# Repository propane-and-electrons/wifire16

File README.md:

wifire16
--------

After I wired up 16 MOSFET + optoisolator circuits on perfboard for Flux and Fire, I swore I was never going to do it by hand again. When it came time to make a similar circuit for Super Street Fire, I decided the only option was to make a PCB to wirelessly control 16 flame effects. The end result: the wifire16 board.

### Feature Summary

* Arduino compatible
* Programmable via 6-pin FTDI header or 6-pin ICSP header
* 16 PWM-capable DC load channels switched via MOSFET
* Wireless support with XBee or compatible radio, e.g. RN-XV WiFly
* All ATMega I/O pins are broken out on the board
* DC load power is optoisolated from the control system power
* Power connectors use 5mm screw terminals or Anderson Powerpole connectors
* Load power status is reported to the microcontroller via an optoisolated input pin
* Output power channels are controlled with a TLC5940 constant current driver that works like a shift register
* Each output channel has a status LED for easy debugging
* TLC5940 control lines are broken out to input/output headers, so boards can be chained without additional control systems

### Design

The wifire16 takes two power inputs: 7-12 volts for the control side, and anything (within reason, e.g. 12 or 24 volts) for the load side. The control system acts exactly like an Arduino with attached XBee/WiFly radio, and is electrically optoisolated from the load side.The independent microcontroller (ATMega328P) on the board can control the power output channels via a pre-programmed routine, interactively over a wireless link, or with external sensors attached to the I/O pins. If more than 16 channels are needed, multiple boards can be chained together and controlled in the same way, with only one control system necessary.

The original purpose of the wifire16 is to control DC-powered solenoid valves for flame effects. The isolation of the two power sources protects the control side from the higher voltage load side, and also allows the load side power to be cut (i.e. by an arming or deadman switch) without affecting the control system. While the system was intended to handle solenoid valves that require 1A+ per channel, it can also be used to control anything else that needs DC power, e.g. motors or 12v LED rope lighting.

### v1 Note

The deprecated v1 version of this board used regular 74595 shift registers and were not PWM capable on all output channels. It also did not have Anderson Powerpole connnectors.

### Documents

* [Schematic](docs/wifire16-schematic.pdf)
* [Bill of Materials](docs/wifire16-BOM.csv)

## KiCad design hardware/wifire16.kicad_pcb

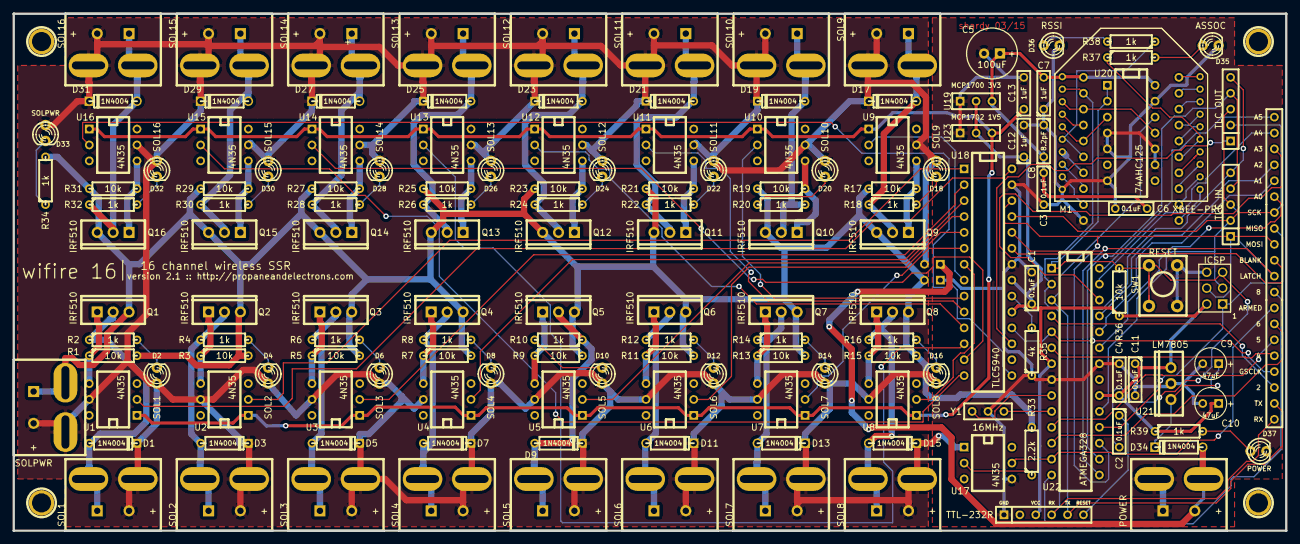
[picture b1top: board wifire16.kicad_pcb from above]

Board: 2 copper layers, 203.2 x 82.5 mm, 164 parts (0 on the bottom side), 120 nets.

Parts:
C1, C2, C3, C4, C6, C11: 0.1uF; C2
C5: 100uF; C1V8
C7, C12, C13: 1uF; C2
C8: 8.2pF; C2
C9, C10: 47uF; C1V5
D1, D3, D5, D7, D9, D11, D13, D15, D17, D19, D21, D23, D25, D27, D29, D31, D34: 1N4004; D3
D2: SOL1; LED-3MM
D4: SOL2; LED-3MM
D6: SOL3; LED-3MM
D8: SOL4; LED-3MM
D10: SOL5; LED-3MM
D12: SOL6; LED-3MM
D14: SOL7; LED-3MM
D16: SOL8; LED-3MM
D18: SOL9; LED-3MM
D20: SOL10; LED-3MM
D22: SOL11; LED-3MM
D24: SOL12; LED-3MM
D26: SOL13; LED-3MM
D28: SOL14; LED-3MM
D30: SOL15; LED-3MM
D32: SOL16; LED-3MM
D33: SOLPWR; LED-3MM
D35: ASSOC; LED-3MM
D36: RSSI; LED-3MM
D37: POWER; LED-3MM
H1, H2, H3, H4: SCREWHOLE; 1pin
JP1: POWER; SIL-2
JP2: GROUND; SIL-2
M1: XBEE-PRO; XBEE
P1: SOL1; PP-2H-5MMSCREWTERM
P2: SOL2; PP-2H-5MMSCREWTERM
P3: SOL3; PP-2H-5MMSCREWTERM
P4: SOL4; PP-2H-5MMSCREWTERM
P5: SOL5; PP-2H-5MMSCREWTERM
P6: SOL6; PP-2H-5MMSCREWTERM
P7: SOL7; PP-2H-5MMSCREWTERM
P8: SOL8; PP-2H-5MMSCREWTERM
P9: SOL9; PP-2H-5MMSCREWTERM
P10: SOL10; PP-2H-5MMSCREWTERM
P11: SOL11; PP-2H-5MMSCREWTERM
P12: SOL12; PP-2H-5MMSCREWTERM
P13: SOL13; PP-2H-5MMSCREWTERM
P14: SOL14; PP-2H-5MMSCREWTERM
P15: SOL15; PP-2H-5MMSCREWTERM
P16: SOL16; PP-2H-5MMSCREWTERM
P17: SOLPWR; PP-2H-5MMSCREWTERM
P18: TLC IN; SIL-5
P19: TLC OUT; SIL-5
P20: TTL-232R; SIL-6
P21: ICSP; pin_array_3x2
P22: XBEE_1; SIL-10
P23: XBEE_2; SIL-10
P24: PORTC; SIL-6
P25: PORTD; SIL-8
P26: PORTB; SIL-6
P27: POWER; PP-2H-5MMSCREWTERM
Q1, Q2, Q3, Q4, Q5, Q6, Q7, Q8, Q9, Q10, Q11, Q12, Q13, Q14, Q15, Q16: IRF510; TO220GDS_VERT
R1, R3, R5, R7, R9, R11, R13, R15, R17, R19, R21, R23, R25, R27, R29, R31, R36: 10k; R3
R2, R4, R6, R8, R10, R12, R14, R16, R18, R20, R22, R24, R26, R28, R30, R32, R34, R37, R38, R39: 1k; R3
R33: 2.2k; R3
R35: 4k; R3
SW1: RESET; SW-6MM-4PIN
U1, U2, U3, U4, U5, U6, U7, U8, U9, U10, U11, U12, U13, U14, U15, U16, U17: 4N35; DIP-6__300
U18: TLC5940; DIP-28__300
U19: MCP1700 3V3; SIL-3
U20: 74AHC125; DIP-14__300
U21: LM7805; 7805
U22: ATMEGA328; DIP-28__300
U23: MCP1702 1V5; SIL-3
Y1: 16MHz; SIL-3

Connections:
+1.5V: C13.1, U1.1, U2.1, U3.1, U4.1, U5.1, U6.1, U7.1, U8.1, U9.1, U10.1, U11.1, U12.1, U13.1, U14.1, U15.1, U16.1, U23.3
+3.3V: C3.1, C5.1, C6.1, C7.2, C8.2, M1.1, P22.1, U19.3, U20.14
+12V: D34.1, JP1.1, P27.2
/ARMED: P25.8, U17.5, U22.13
/BLANK: P18.4, P19.4, P26.3, U18.23, U22.16
/GSCLK: P18.5, P19.5, P25.4, U18.18, U22.5
/MISO: P21.1, P26.5, U22.18
/MOSI: P18.1, P21.4, P26.4, U18.26, U22.17
/RESET: C2.2, P21.5, R36.2, SW1.1, SW1.2, U20.1, U20.2, U22.1
/RXD: M1.2, P20.4, P22.2, P25.1, U22.2
/SCK: P18.2, P19.2, P21.3, P26.6, U18.25, U22.19
/SOL1: U1.2, U18.28
/SOL2: U2.2, U18.1
/SOL3: U3.2, U18.2
/SOL4: U4.2, U18.3
/SOL5: U5.2, U18.4
/SOL6: U6.2, U18.5
/SOL7: U7.2, U18.6
/SOL8: U8.2, U18.7
/SOL9: U9.2, U18.8
/SOL10: U10.2, U18.9
/SOL11: U11.2, U18.10
/SOL12: U12.2, U18.11
/SOL13: U13.2, U18.12
/SOL14: U14.2, U18.13
/SOL15: U15.2, U18.14
/SOL16: U16.2, U18.15
/SOLPWR+: D1.2, D2.1, D3.2, D4.1, D5.2, D6.1, D7.2, D8.1, D9.2, D10.1, D11.2, D12.1, D13.2, D14.1, D15.2, D16.1, D17.2, D18.1, D19.2, D20.1, D21.2, D22.1, D23.2, D24.1, D25.2, D26.1, D27.2, D28.1, D29.2, D30.1, D31.2, D32.1, D33.1, JP1.2, P1.2, P2.2, P3.2, P4.2, P5.2, P6.2, P7.2, P8.2, P9.2, P10.2, P11.2, P12.2, P13.2, P14.2, P15.2, P16.2, P17.2, U1.5, U2.5, U3.5, U4.5, U5.5, U6.5, U7.5, U8.5, U9.5, U10.5, U11.5, U12.5, U13.5, U14.5, U15.5, U16.5, U17.1
/SOLPWR-: JP2.2, P17.1, Q1.S, Q2.S, Q3.S, Q4.S, Q5.S, Q6.S, Q7.S, Q8.S, Q9.S, Q10.S, Q11.S, Q12.S, Q13.S, Q14.S, Q15.S, Q16.S, R1.2, R3.2, R5.2, R7.2, R9.2, R11.2, R13.2, R15.2, R17.2, R19.2, R21.2, R23.2, R25.2, R27.2, R29.2, R31.2, R33.2, R34.2
/SOUT: P19.1, U18.17
/TXD: P20.5, P25.2, U20.12, U22.3
/XLAT: P18.3, P19.3, P26.2, U18.24, U22.15
GND: C1.2, C3.2, C4.2, C5.2, C6.2, C7.1, C8.1, C9.2, C10.2, C11.2, C12.2, C13.2, D35.2, D36.2, D37.2, JP2.1, M1.10, P20.1, P21.6, P22.10, P27.1, R35.1, SW1.3, SW1.4, U17.4, U18.22, U18.27, U19.1, U20.4, U20.5, U20.7, U20.9, U20.10, U20.13, U21.2, U22.8, U22.22, U23.1, Y1.2
unnamed: C2.1, P20.6
unnamed: C9.1, D34.2, U21.1
unnamed: D1.1, P1.1, Q1.D, R2.1
unnamed: D2.2, R2.2
unnamed: D3.1, P2.1, Q2.D, R4.1
unnamed: D4.2, R4.2
unnamed: D5.1, P3.1, Q3.D, R6.1
unnamed: D6.2, R6.2
unnamed: D7.1, P4.1, Q4.D, R8.1
unnamed: D8.2, R8.2
unnamed: D9.1, P5.1, Q5.D, R10.1
unnamed: D10.2, R10.2
unnamed: D11.1, P6.1, Q6.D, R12.1
unnamed: D12.2, R12.2
unnamed: D13.1, P7.1, Q7.D, R14.1
unnamed: D14.2, R14.2
unnamed: D15.1, P8.1, Q8.D, R16.1
unnamed: D16.2, R16.2
unnamed: D17.1, P9.1, Q9.D, R18.1
unnamed: D18.2, R18.2
unnamed: D19.1, P10.1, Q10.D, R20.1
unnamed: D20.2, R20.2
unnamed: D21.1, P11.1, Q11.D, R22.1
unnamed: D22.2, R22.2
unnamed: D23.1, P12.1, Q12.D, R24.1
unnamed: D24.2, R24.2
unnamed: D25.1, P13.1, Q13.D, R26.1
unnamed: D26.2, R26.2
unnamed: D27.1, P14.1, Q14.D, R28.1
unnamed: D28.2, R28.2
unnamed: D29.1, P15.1, Q15.D, R30.1
unnamed: D30.2, R30.2
unnamed: D31.1, P16.1, Q16.D, R32.1
unnamed: D32.2, R32.2
unnamed: D33.2, R34.1
unnamed: D35.1, R37.2
unnamed: D36.1, R38.2
unnamed: D37.1, R39.2
unnamed: M1.3, P22.3, U20.11
unnamed: M1.4, P22.4
unnamed: M1.5, P22.5, U20.3
unnamed: M1.6, P22.6, R38.1
unnamed: M1.7, P22.7
unnamed: M1.8, P22.8
unnamed: M1.9, P22.9
unnamed: M1.11, P23.1
unnamed: M1.12, P23.2
unnamed: M1.13, P23.3
unnamed: M1.14, P23.4
unnamed: M1.15, P23.5, R37.1
unnamed: M1.16, P23.6
unnamed: M1.17, P23.7
unnamed: M1.18, P23.8
unnamed: M1.19, P23.9
unnamed: M1.20, P23.10
unnamed: P24.1, U22.23
unnamed: P24.2, U22.24
unnamed: P24.3, U22.25
unnamed: P24.4, U22.26
unnamed: P24.5, U22.27
unnamed: P24.6, U22.28
unnamed: P25.3, U22.4
unnamed: P25.5, U22.6
unnamed: P25.6, U22.11
unnamed: P25.7, U22.12
unnamed: P26.1, U22.14
unnamed: Q1.G, R1.1, U1.4
unnamed: Q2.G, R3.1, U2.4
unnamed: Q3.G, R5.1, U3.4
unnamed: Q4.G, R7.1, U4.4
unnamed: Q5.G, R9.1, U5.4
unnamed: Q6.G, R11.1, U6.4
unnamed: Q7.G, R13.1, U7.4
unnamed: Q8.G, R15.1, U8.4
unnamed: Q9.G, R17.1, U9.4
unnamed: Q10.G, R19.1, U10.4
unnamed: Q11.G, R21.1, U11.4
unnamed: Q12.G, R23.1, U12.4
unnamed: Q13.G, R25.1, U13.4
unnamed: Q14.G, R27.1, U14.4
unnamed: Q15.G, R29.1, U15.4
unnamed: Q16.G, R31.1, U16.4
unnamed: R33.1, U17.2
unnamed: R35.2, U18.20
unnamed: U22.9, Y1.1
unnamed: U22.10, Y1.3
VCC: C1.1, C4.1, C10.1, C11.1, C12.1, P20.3, P21.2, R36.1, R39.1, U18.19, U18.21, U19.2, U21.3, U22.7, U22.20, U23.2

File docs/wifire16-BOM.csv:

Designator,Package,Quantity,Part,Digi-Key Part
"C1,C2,C3,C4,C6,C11",C2,6,0.1uF,490-5388-ND
C5,C1V8,1,100uF,P13459-ND
"C7,C12,C13",C2,3,1uF,445-2858-ND
C8,C2,1,8.2pF,490-3764-ND
"C9,C10",C1V5,2,47uF,P13464-ND
"D2,D4,D6,D8,D10,D12,D14,D16,D18,D20,D22,D24,D26,D28,D30,D32,D33",LED-3MM,17,LED 3mm (red),754-1606-ND
"D1,D3,D5,D7,D9,D11,D13,D15,D17,D19,D21,D23,D25,D27,D29,D31,D34",D3,17,1N4004,641-1311-1-ND
"D35,D36,D37",LED-3MM,3,LED 3mm (green),754-1603-ND
"JP1,JP2,P20","SIL-2, SIL-6",10,header pins,A34253-40-ND
M1,XBEE,1,RN-XV,740-1044-ND
"P1-P17,P27",PP-2H-5MMSCREWTERM,18,5mm screw terminals or Anderson Powerpole connectors,ED2600-ND
P21,pin_array_3x2,3,2x header pins,A34344-40-ND
Q1-Q17,TO220GDS_VERT,16,IRF510,IRF510PBF-ND
"R1,R3,R5,R7,R9,R11,R13,R15,R17,R19,R21,R23,R25,R27,R29,R31,R36",R3,17,10k,10KQBK-ND
"R2,R4,R6,R8,R10,R12,R14,R16,R18,R20,R22,R24,R26,R28,R30,R32,R34,R37,R38,R39",R3,20,1k,1.0KQBK-ND
R33,R3,1,2.2k,2.2QBK-ND
R35,R3,1,4k,not in stock?!
SW1,SW-6MM-4PIN,1,momentary pushbutton,SW400-ND
U1-U17,DIP-6__300,17,4N35,516-1557-5-ND
U18,DIP-28__300,1,TLC5940,296-17732-5-ND
U19,SIL-3,1,MCP1700,MCP1700-3302E/TO-ND
U20,DIP-14__300,1,74AHC125,296-4531-5-ND
U21,7805,1,LM7805,LM7805CT-ND
U22,DIP-28__300,1,ATMEGA328,ATMEGA328P-PU-ND
U23,SIL-3,1,MCP1702,MCP1702-1502E/TO-ND
"XM1A,XM1B",,2,10pin 2mm header,S5751-10-ND
XU1-XU17,6-DIP,17,6-DIP socket,A100203-ND
Y1,SIL-3,1,16MHz,490-1214-ND

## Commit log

2013-03-26 initial commit - need to clean this up, but at least getting it into the repo
2013-05-12 minissc relay script
2014-01-05 moving things around
2014-01-05 2.0 revisions - swapped powerpole direction (and diodes), backannotated schematic with footprints, other fixups
2014-01-05 a few more file changes
2014-01-05 adding documentation
2014-01-30 typo
2015-03-11 fixing bugs, using a new version of kicad
2015-03-11 updating to 2.1 docs
2015-03-14 removing unused pin name
2015-05-13 fixing zone clearances
